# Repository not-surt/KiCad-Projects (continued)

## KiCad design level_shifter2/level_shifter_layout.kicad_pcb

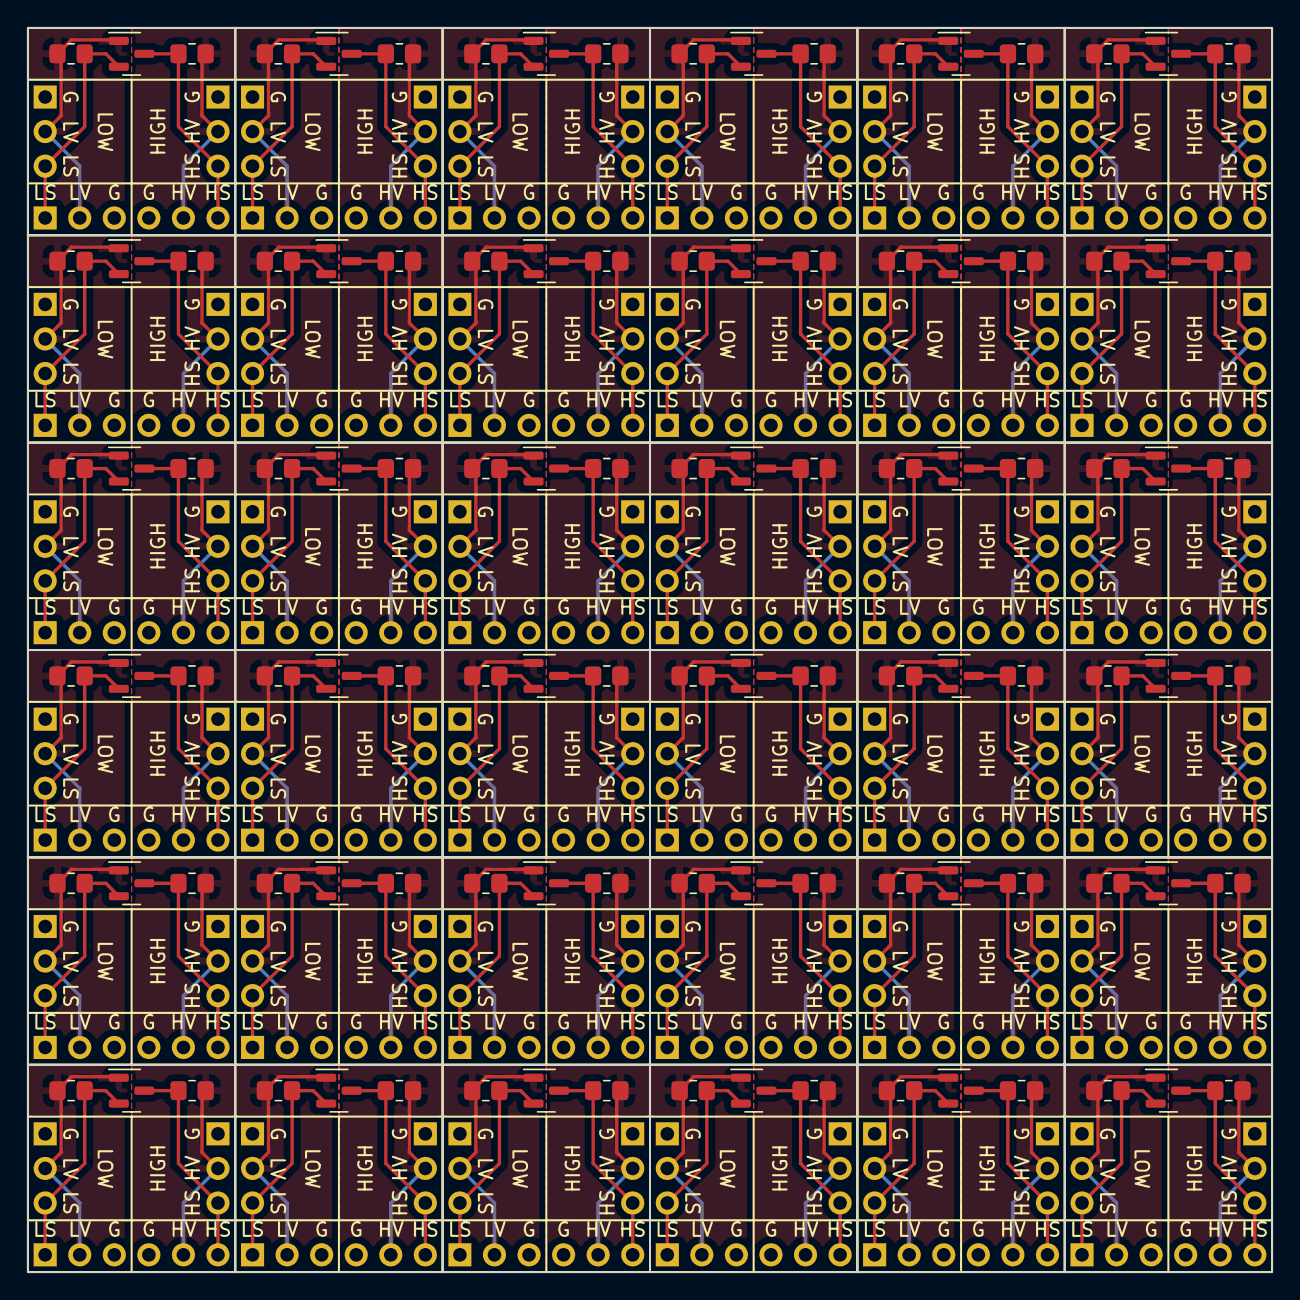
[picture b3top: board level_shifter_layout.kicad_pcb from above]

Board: 2 copper layers, 91.4 x 91.4 mm, 216 parts (0 on the bottom side), 5 nets.

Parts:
J1, J2, J3, J5, J7, J8, J10, J11, J13, J14, J16, J17, J25, J26, J28, J29, J31, J32, J34, J35, J37, J38, J40, J41, J49, J50, J52, J53, J55, J56, J58, J59, J61, J62, J64, J65, J73, J74, J76, J77, J79, J80, J82, J83, J85, J86, J88, J89, J97, J98, J100, J101, J103, J104, J106, J107, J109, J110, J112, J113, J121, J122, J124, J125, J127, J128, J130, J131, J133, J134, J136, J137: Conn_01x03; PinHeader_1x03_P2.54mm_Vertical_no_silk
J4, J6, J9, J12, J15, J18, J27, J30, J33, J36, J39, J42, J51, J54, J57, J60, J63, J66, J75, J78, J81, J84, J87, J90, J99, J102, J105, J108, J111, J114, J123, J126, J129, J132, J135, J138: Conn_01x06; PinHeader_1x06_P2.54mm_Vertical_no_silk
Q1, Q2, Q3, Q4, Q5, Q6, Q9, Q10, Q11, Q12, Q13, Q14, Q17, Q18, Q19, Q20, Q21, Q22, Q25, Q26, Q27, Q28, Q29, Q30, Q33, Q34, Q35, Q36, Q37, Q38, Q41, Q42, Q43, Q44, Q45, Q46: BSS138; SOT-23
R1, R2, R3, R4, R5, R6, R7, R8, R9, R10, R11, R12, R17, R18, R19, R20, R21, R22, R23, R24, R25, R26, R27, R28, R33, R34, R35, R36, R37, R38, R39, R40, R41, R42, R43, R44, R49, R50, R51, R52, R53, R54, R55, R56, R57, R58, R59, R60, R65, R66, R67, R68, R69, R70, R71, R72, R73, R74, R75, R76, R81, R82, R83, R84, R85, R86, R87, R88, R89, R90, R91, R92: 10K; R_0805_2012Metric_Pad1.20x1.40mm_HandSolder

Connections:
G: J1.1, J2.1, J3.1, J4.3, J4.4, J5.1, J6.3, J6.4, J7.1, J8.1, J9.3, J9.4, J10.1, J11.1, J12.3, J12.4, J13.1, J14.1, J15.3, J15.4, J16.1, J17.1, J18.3, J18.4, J25.1, J26.1, J27.3, J27.4, J28.1, J29.1, J30.3, J30.4, J31.1, J32.1, J33.3, J33.4, J34.1, J35.1, J36.3, J36.4, J37.1, J38.1, J39.3, J39.4, J40.1, J41.1, J42.3, J42.4, J49.1, J50.1, J51.3, J51.4, J52.1, J53.1, J54.3, J54.4, J55.1, J56.1, J57.3, J57.4, J58.1, J59.1, J60.3, J60.4, J61.1, J62.1, J63.3, J63.4, J64.1, J65.1, J66.3, J66.4, J73.1, J74.1, J75.3, J75.4, J76.1, J77.1, J78.3, J78.4, J79.1, J80.1, J81.3, J81.4, J82.1, J83.1, J84.3, J84.4, J85.1, J86.1, J87.3, J87.4, J88.1, J89.1, J90.3, J90.4, J97.1, J98.1, J99.3, J99.4, J100.1, J101.1, J102.3, J102.4, J103.1, J104.1, J105.3, J105.4, J106.1, J107.1, J108.3, J108.4, J109.1, J110.1, J111.3, J111.4, J112.1, J113.1, J114.3, J114.4, J121.1, J122.1, J123.3, J123.4, J124.1, J125.1, J126.3, J126.4, J127.1, J128.1, J129.3, J129.4, J130.1, J131.1, J132.3, J132.4, J133.1, J134.1, J135.3, J135.4, J136.1, J137.1, J138.3, J138.4
HS: J2.3, J4.6, J5.3, J6.6, J8.3, J9.6, J11.3, J12.6, J14.3, J15.6, J17.3, J18.6, J26.3, J27.6, J29.3, J30.6, J32.3, J33.6, J35.3, J36.6, J38.3, J39.6, J41.3, J42.6, J50.3, J51.6, J53.3, J54.6, J56.3, J57.6, J59.3, J60.6, J62.3, J63.6, J65.3, J66.6, J74.3, J75.6, J77.3, J78.6, J80.3, J81.6, J83.3, J84.6, J86.3, J87.6, J89.3, J90.6, J98.3, J99.6, J101.3, J102.6, J104.3, J105.6, J107.3, J108.6, J110.3, J111.6, J113.3, J114.6, J122.3, J123.6, J125.3, J126.6, J128.3, J129.6, J131.3, J132.6, J134.3, J135.6, J137.3, J138.6, Q1.3 (D), Q2.3 (D), Q3.3 (D), Q4.3 (D), Q5.3 (D), Q6.3 (D), Q9.3 (D), Q10.3 (D), Q11.3 (D), Q12.3 (D), Q13.3 (D), Q14.3 (D), Q17.3 (D), Q18.3 (D), Q19.3 (D), Q20.3 (D), Q21.3 (D), Q22.3 (D), Q25.3 (D), Q26.3 (D), Q27.3 (D), Q28.3 (D), Q29.3 (D), Q30.3 (D), Q33.3 (D), Q34.3 (D), Q35.3 (D), Q36.3 (D), Q37.3 (D), Q38.3 (D), Q41.3 (D), Q42.3 (D), Q43.3 (D), Q44.3 (D), Q45.3 (D), Q46.3 (D), R2.2, R4.2, R6.2, R8.2, R10.2, R12.2, R18.2, R20.2, R22.2, R24.2, R26.2, R28.2, R34.2, R36.2, R38.2, R40.2, R42.2, R44.2, R50.2, R52.2, R54.2, R56.2, R58.2, R60.2, R66.2, R68.2, R70.2, R72.2, R74.2, R76.2, R82.2, R84.2, R86.2, R88.2, R90.2, R92.2
HV: J2.2, J4.5, J5.2, J6.5, J8.2, J9.5, J11.2, J12.5, J14.2, J15.5, J17.2, J18.5, J26.2, J27.5, J29.2, J30.5, J32.2, J33.5, J35.2, J36.5, J38.2, J39.5, J41.2, J42.5, J50.2, J51.5, J53.2, J54.5, J56.2, J57.5, J59.2, J60.5, J62.2, J63.5, J65.2, J66.5, J74.2, J75.5, J77.2, J78.5, J80.2, J81.5, J83.2, J84.5, J86.2, J87.5, J89.2, J90.5, J98.2, J99.5, J101.2, J102.5, J104.2, J105.5, J107.2, J108.5, J110.2, J111.5, J113.2, J114.5, J122.2, J123.5, J125.2, J126.5, J128.2, J129.5, J131.2, J132.5, J134.2, J135.5, J137.2, J138.5, R2.1, R4.1, R6.1, R8.1, R10.1, R12.1, R18.1, R20.1, R22.1, R24.1, R26.1, R28.1, R34.1, R36.1, R38.1, R40.1, R42.1, R44.1, R50.1, R52.1, R54.1, R56.1, R58.1, R60.1, R66.1, R68.1, R70.1, R72.1, R74.1, R76.1, R82.1, R84.1, R86.1, R88.1, R90.1, R92.1
LS: J1.3, J3.3, J4.1, J6.1, J7.3, J9.1, J10.3, J12.1, J13.3, J15.1, J16.3, J18.1, J25.3, J27.1, J28.3, J30.1, J31.3, J33.1, J34.3, J36.1, J37.3, J39.1, J40.3, J42.1, J49.3, J51.1, J52.3, J54.1, J55.3, J57.1, J58.3, J60.1, J61.3, J63.1, J64.3, J66.1, J73.3, J75.1, J76.3, J78.1, J79.3, J81.1, J82.3, J84.1, J85.3, J87.1, J88.3, J90.1, J97.3, J99.1, J100.3, J102.1, J103.3, J105.1, J106.3, J108.1, J109.3, J111.1, J112.3, J114.1, J121.3, J123.1, J124.3, J126.1, J127.3, J129.1, J130.3, J132.1, J133.3, J135.1, J136.3, J138.1, Q1.2 (S), Q2.2 (S), Q3.2 (S), Q4.2 (S), Q5.2 (S), Q6.2 (S), Q9.2 (S), Q10.2 (S), Q11.2 (S), Q12.2 (S), Q13.2 (S), Q14.2 (S), Q17.2 (S), Q18.2 (S), Q19.2 (S), Q20.2 (S), Q21.2 (S), Q22.2 (S), Q25.2 (S), Q26.2 (S), Q27.2 (S), Q28.2 (S), Q29.2 (S), Q30.2 (S), Q33.2 (S), Q34.2 (S), Q35.2 (S), Q36.2 (S), Q37.2 (S), Q38.2 (S), Q41.2 (S), Q42.2 (S), Q43.2 (S), Q44.2 (S), Q45.2 (S), Q46.2 (S), R1.2, R3.2, R5.2, R7.2, R9.2, R11.2, R17.2, R19.2, R21.2, R23.2, R25.2, R27.2, R33.2, R35.2, R37.2, R39.2, R41.2, R43.2, R49.2, R51.2, R53.2, R55.2, R57.2, R59.2, R65.2, R67.2, R69.2, R71.2, R73.2, R75.2, R81.2, R83.2, R85.2, R87.2, R89.2, R91.2
LV: J1.2, J3.2, J4.2, J6.2, J7.2, J9.2, J10.2, J12.2, J13.2, J15.2, J16.2, J18.2, J25.2, J27.2, J28.2, J30.2, J31.2, J33.2, J34.2, J36.2, J37.2, J39.2, J40.2, J42.2, J49.2, J51.2, J52.2, J54.2, J55.2, J57.2, J58.2, J60.2, J61.2, J63.2, J64.2, J66.2, J73.2, J75.2, J76.2, J78.2, J79.2, J81.2, J82.2, J84.2, J85.2, J87.2, J88.2, J90.2, J97.2, J99.2, J100.2, J102.2, J103.2, J105.2, J106.2, J108.2, J109.2, J111.2, J112.2, J114.2, J121.2, J123.2, J124.2, J126.2, J127.2, J129.2, J130.2, J132.2, J133.2, J135.2, J136.2, J138.2, Q1.1 (G), Q2.1 (G), Q3.1 (G), Q4.1 (G), Q5.1 (G), Q6.1 (G), Q9.1 (G), Q10.1 (G), Q11.1 (G), Q12.1 (G), Q13.1 (G), Q14.1 (G), Q17.1 (G), Q18.1 (G), Q19.1 (G), Q20.1 (G), Q21.1 (G), Q22.1 (G), Q25.1 (G), Q26.1 (G), Q27.1 (G), Q28.1 (G), Q29.1 (G), Q30.1 (G), Q33.1 (G), Q34.1 (G), Q35.1 (G), Q36.1 (G), Q37.1 (G), Q38.1 (G), Q41.1 (G), Q42.1 (G), Q43.1 (G), Q44.1 (G), Q45.1 (G), Q46.1 (G), R1.1, R3.1, R5.1, R7.1, R9.1, R11.1, R17.1, R19.1, R21.1, R23.1, R25.1, R27.1, R33.1, R35.1, R37.1, R39.1, R41.1, R43.1, R49.1, R51.1, R53.1, R55.1, R57.1, R59.1, R65.1, R67.1, R69.1, R71.1, R73.1, R75.1, R81.1, R83.1, R85.1, R87.1, R89.1, R91.1

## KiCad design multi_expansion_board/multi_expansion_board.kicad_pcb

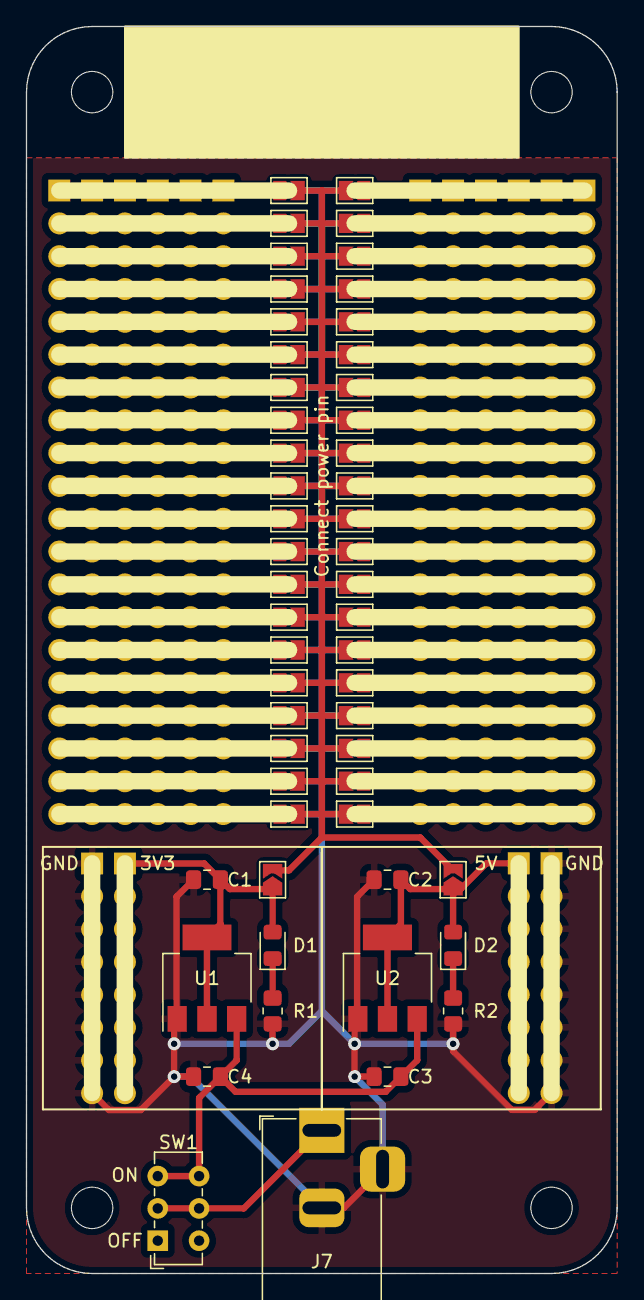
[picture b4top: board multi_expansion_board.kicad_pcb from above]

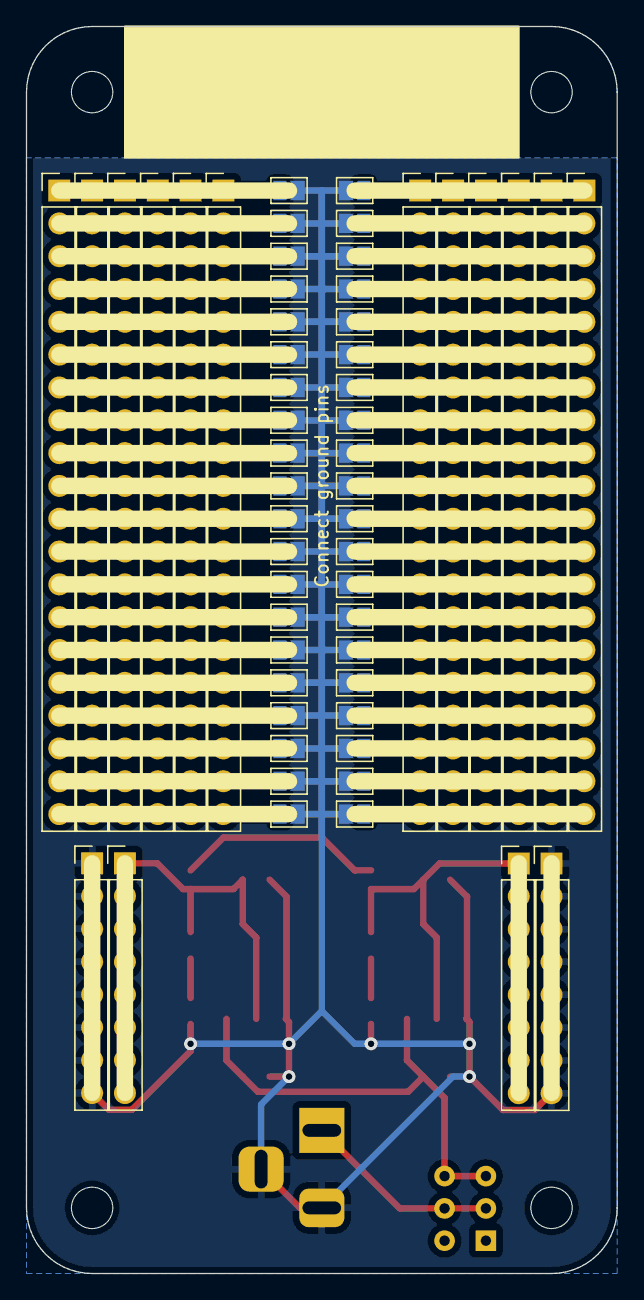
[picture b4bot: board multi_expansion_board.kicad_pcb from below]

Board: 2 copper layers, 45.7 x 96.5 mm, 110 parts (56 on the bottom side), 48 nets.

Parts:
C1, C2, C3, C4: 10uF; C_0805_2012Metric_Pad1.18x1.45mm_HandSolder
D1, D2: LED; LED_0805_2012Metric_Pad1.15x1.40mm_HandSolder
J1, J2, J3, J4, J5, J6, J8, J9, J10, J11, J12, J13: Conn_01x20; PinHeader_1x20_P2.54mm_Vertical
J7: Barrel_Jack; BarrelJack_Horizontal
J14, J15, J16, J17: Conn_01x08; PinHeader_1x08_P2.54mm_Vertical
JP1, JP2, JP3, JP4, JP5, JP6, JP7, JP8, JP9, JP10, JP11, JP12, JP13, JP14, JP15, JP16, JP17, JP18, JP19, JP20, JP21, JP22, JP23, JP24, JP25, JP26, JP27, JP28, JP29, JP30, JP31, JP32, JP33, JP34, JP35, JP36, JP37, JP38, JP39, JP40, JP41, JP42, JP43, JP44, JP45, JP46, JP47, JP48, JP49, JP50, JP51, JP52, JP53, JP54, JP55, JP56, JP57, JP58, JP59, JP60, JP61, JP62, JP63, JP64, JP65, JP66, JP67, JP68, JP69, JP70, JP71, JP72, JP73, JP74, JP75, JP76, JP77, JP78, JP79, JP80, JP81, JP82: SolderJumper_2_Open; SolderJumper-2_P1.3mm_Open_TrianglePad1.0x1.5mm
R1, R2: R; R_0805_2012Metric_Pad1.20x1.40mm_HandSolder
SW1: SW_SPST; SW_E-Switch_EG1271_DPDT
U1: AMS1117-3.3; SOT-223-3_TabPin2
U2: AMS1117-5.0; SOT-223-3_TabPin2

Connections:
+3.3V: C1.1, D1.2 (A), J15.1, J15.2, J15.3, J15.4, J15.5, J15.6, J15.7, J15.8, JP81.1 (A), U1.2 (VO)
+5V: C2.1, D2.2 (A), J16.1, J16.2, J16.3, J16.4, J16.5, J16.6, J16.7, J16.8, JP82.1 (A), U2.2 (VO)
GND: C1.2, C2.2, C3.2, C4.2, J7.2, J7.3, J14.1, J14.2, J14.3, J14.4, J14.5, J14.6, J14.7, J14.8, J17.1, J17.2, J17.3, J17.4, J17.5, J17.6, J17.7, J17.8, JP3.2 (B), JP4.2 (B), JP7.2 (B), JP8.2 (B), JP11.2 (B), JP12.2 (B), JP15.2 (B), JP16.2 (B), JP19.2 (B), JP20.2 (B), JP23.2 (B), JP24.2 (B), JP27.2 (B), JP28.2 (B), JP31.2 (B), JP32.2 (B), JP35.2 (B), JP36.2 (B), JP39.2 (B), JP40.2 (B), JP43.2 (B), JP44.2 (B), JP47.2 (B), JP48.2 (B), JP51.2 (B), JP52.2 (B), JP55.2 (B), JP56.2 (B), JP59.2 (B), JP60.2 (B), JP63.2 (B), JP64.2 (B), JP67.2 (B), JP68.2 (B), JP71.2 (B), JP72.2 (B), JP75.2 (B), JP76.2 (B), JP79.2 (B), JP80.2 (B), R1.2, R2.2, U1.1 (GND), U2.1 (GND)
unnamed: D1.1 (K), R1.1
unnamed: D2.1 (K), R2.1
unnamed: J1.1, J2.1, J3.1, J4.1, J5.1, J6.1, JP1.1 (A), JP3.1 (A)
unnamed: J1.2, J2.2, J3.2, J4.2, J5.2, J6.2, JP5.1 (A), JP7.1 (A)
unnamed: J1.3, J2.3, J3.3, J4.3, J5.3, J6.3, JP9.1 (A), JP11.1 (A)
unnamed: J1.4, J2.4, J3.4, J4.4, J5.4, J6.4, JP13.1 (A), JP15.1 (A)
unnamed: J1.5, J2.5, J3.5, J4.5, J5.5, J6.5, JP17.1 (A), JP19.1 (A)
unnamed: J1.6, J2.6, J3.6, J4.6, J5.6, J6.6, JP21.1 (A), JP23.1 (A)
unnamed: J1.7, J2.7, J3.7, J4.7, J5.7, J6.7, JP25.1 (A), JP27.1 (A)
unnamed: J1.8, J2.8, J3.8, J4.8, J5.8, J6.8, JP29.1 (A), JP31.1 (A)
unnamed: J1.9, J2.9, J3.9, J4.9, J5.9, J6.9, JP33.1 (A), JP35.1 (A)
unnamed: J1.10, J2.10, J3.10, J4.10, J5.10, J6.10, JP37.1 (A), JP39.1 (A)
unnamed: J1.11, J2.11, J3.11, J4.11, J5.11, J6.11, JP41.1 (A), JP43.1 (A)
unnamed: J1.12, J2.12, J3.12, J4.12, J5.12, J6.12, JP45.1 (A), JP47.1 (A)
unnamed: J1.13, J2.13, J3.13, J4.13, J5.13, J6.13, JP49.1 (A), JP51.1 (A)
unnamed: J1.14, J2.14, J3.14, J4.14, J5.14, J6.14, JP53.1 (A), JP55.1 (A)
unnamed: J1.15, J2.15, J3.15, J4.15, J5.15, J6.15, JP57.1 (A), JP59.1 (A)
unnamed: J1.16, J2.16, J3.16, J4.16, J5.16, J6.16, JP61.1 (A), JP63.1 (A)
unnamed: J1.17, J2.17, J3.17, J4.17, J5.17, J6.17, JP65.1 (A), JP67.1 (A)
unnamed: J1.18, J2.18, J3.18, J4.18, J5.18, J6.18, JP69.1 (A), JP71.1 (A)
unnamed: J1.19, J2.19, J3.19, J4.19, J5.19, J6.19, JP73.1 (A), JP75.1 (A)
unnamed: J1.20, J2.20, J3.20, J4.20, J5.20, J6.20, JP77.1 (A), JP79.1 (A)
unnamed: J7.1, SW1.2 (B), SW1.5
unnamed: J8.1, J9.1, J10.1, J11.1, J12.1, J13.1, JP2.1 (A), JP4.1 (A)
unnamed: J8.2, J9.2, J10.2, J11.2, J12.2, J13.2, JP6.1 (A), JP8.1 (A)
unnamed: J8.3, J9.3, J10.3, J11.3, J12.3, J13.3, JP10.1 (A), JP12.1 (A)
unnamed: J8.4, J9.4, J10.4, J11.4, J12.4, J13.4, JP14.1 (A), JP16.1 (A)
unnamed: J8.5, J9.5, J10.5, J11.5, J12.5, J13.5, JP18.1 (A), JP20.1 (A)
unnamed: J8.6, J9.6, J10.6, J11.6, J12.6, J13.6, JP22.1 (A), JP24.1 (A)
unnamed: J8.7, J9.7, J10.7, J11.7, J12.7, J13.7, JP26.1 (A), JP28.1 (A)
unnamed: J8.8, J9.8, J10.8, J11.8, J12.8, J13.8, JP30.1 (A), JP32.1 (A)
unnamed: J8.9, J9.9, J10.9, J11.9, J12.9, J13.9, JP34.1 (A), JP36.1 (A)
unnamed: J8.10, J9.10, J10.10, J11.10, J12.10, J13.10, JP38.1 (A), JP40.1 (A)
unnamed: J8.11, J9.11, J10.11, J11.11, J12.11, J13.11, JP42.1 (A), JP44.1 (A)
unnamed: J8.12, J9.12, J10.12, J11.12, J12.12, J13.12, JP46.1 (A), JP48.1 (A)
unnamed: J8.13, J9.13, J10.13, J11.13, J12.13, J13.13, JP50.1 (A), JP52.1 (A)
unnamed: J8.14, J9.14, J10.14, J11.14, J12.14, J13.14, JP54.1 (A), JP56.1 (A)
unnamed: J8.15, J9.15, J10.15, J11.15, J12.15, J13.15, JP58.1 (A), JP60.1 (A)
unnamed: J8.16, J9.16, J10.16, J11.16, J12.16, J13.16, JP62.1 (A), JP64.1 (A)
unnamed: J8.17, J9.17, J10.17, J11.17, J12.17, J13.17, JP66.1 (A), JP68.1 (A)
unnamed: J8.18, J9.18, J10.18, J11.18, J12.18, J13.18, JP70.1 (A), JP72.1 (A)
unnamed: J8.19, J9.19, J10.19, J11.19, J12.19, J13.19, JP74.1 (A), JP76.1 (A)
unnamed: J8.20, J9.20, J10.20, J11.20, J12.20, J13.20, JP78.1 (A), JP80.1 (A)
unnamed: JP1.2 (B), JP2.2 (B), JP5.2 (B), JP6.2 (B), JP9.2 (B), JP10.2 (B), JP13.2 (B), JP14.2 (B), JP17.2 (B), JP18.2 (B), JP21.2 (B), JP22.2 (B), JP25.2 (B), JP26.2 (B), JP29.2 (B), JP30.2 (B), JP33.2 (B), JP34.2 (B), JP37.2 (B), JP38.2 (B), JP41.2 (B), JP42.2 (B), JP45.2 (B), JP46.2 (B), JP49.2 (B), JP50.2 (B), JP53.2 (B), JP54.2 (B), JP57.2 (B), JP58.2 (B), JP61.2 (B), JP62.2 (B), JP65.2 (B), JP66.2 (B), JP69.2 (B), JP70.2 (B), JP73.2 (B), JP74.2 (B), JP77.2 (B), JP78.2 (B), JP81.2 (B), JP82.2 (B)
VCC: C3.1, C4.1, SW1.3, SW1.6, U1.3 (VI), U2.3 (VI)

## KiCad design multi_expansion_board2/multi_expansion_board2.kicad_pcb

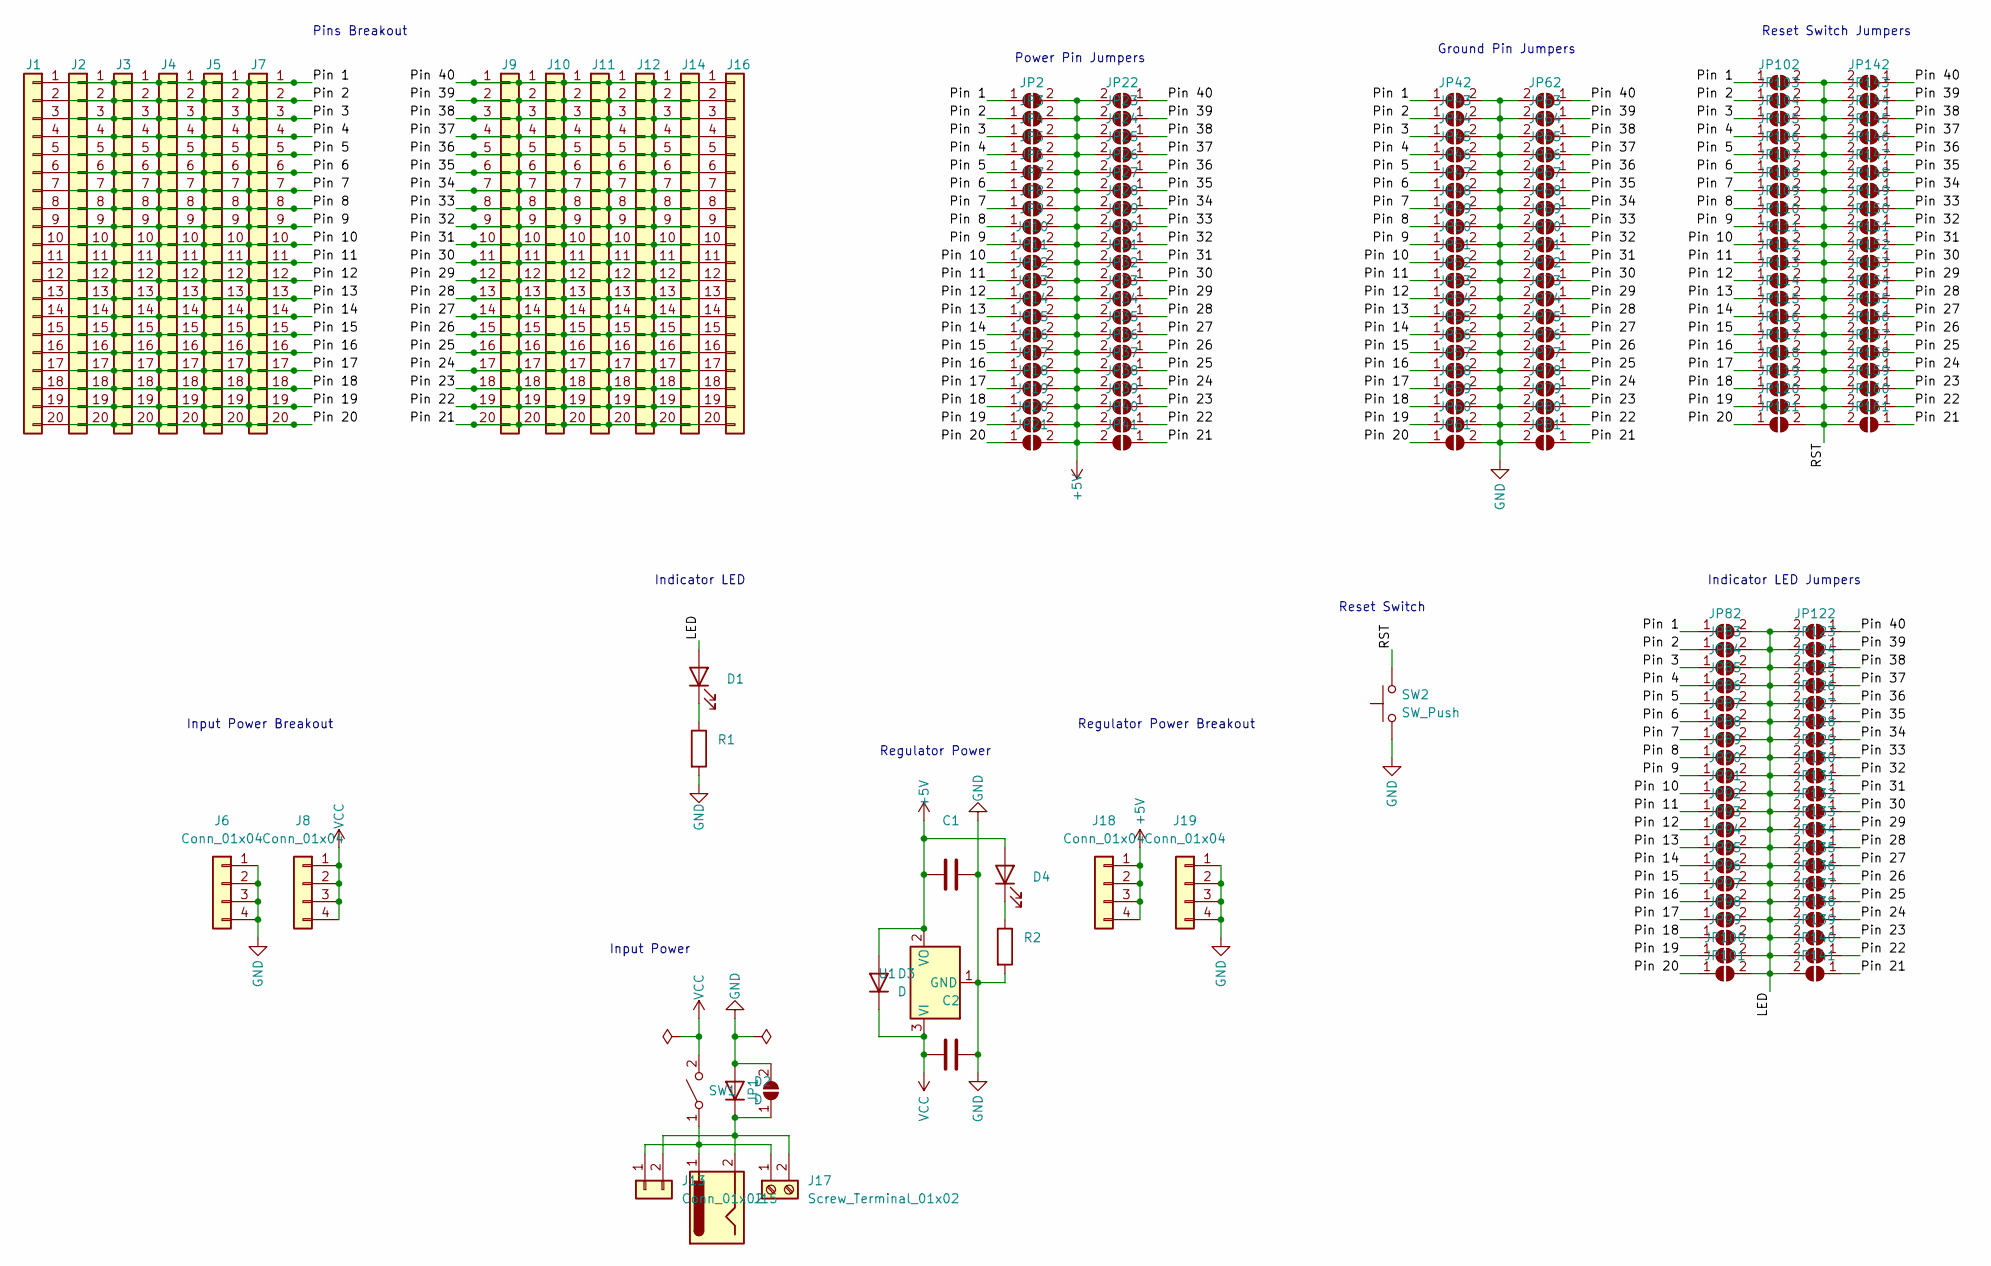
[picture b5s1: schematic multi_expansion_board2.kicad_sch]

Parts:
C1, C2: 10uF; C_0805_2012Metric_Pad1.18x1.45mm_HandSolder
D1, D4: LED; LED_0805_2012Metric_Pad1.15x1.40mm_HandSolder
D2, D3: D; D_SMA_Handsoldering
J1, J2, J3, J4, J5, J7, J9, J10, J11, J12, J14, J16: Conn_01x20; PinHeader_1x20_P2.54mm_Vertical
J6, J8, J18, J19: Conn_01x04; PinHeader_1x08_P2.54mm_Vertical
J13: Conn_01x02; PinHeader_1x02_P2.54mm_Vertical
J15: Barrel_Jack; BarrelJack_Horizontal
J17: Screw_Terminal_01x02; TerminalBlock_bornier-2_P5.08mm
JP1, JP2, JP3, JP4, JP5, JP6, JP7, JP8, JP9, JP10, JP11, JP12, JP13, JP14, JP15, JP16, JP17, JP18, JP19, JP20, JP21, JP22, JP23, JP24, JP25, JP26, JP27, JP28, JP29, JP30, JP31, JP32, JP33, JP34, JP35, JP36, JP37, JP38, JP39, JP40, JP41, JP42, JP43, JP44, JP45, JP46, JP47, JP48, JP49, JP50, JP51, JP52, JP53, JP54, JP55, JP56, JP57, JP58, JP59, JP60, JP61, JP62, JP63, JP64, JP65, JP66, JP67, JP68, JP69, JP70, JP71, JP72, JP73, JP74, JP75, JP76, JP77, JP78, JP79, JP80, JP81, JP82, JP83, JP84, JP85, JP86, JP87, JP88, JP89, JP90, JP91, JP92, JP93, JP94, JP95, JP96, JP97, JP98, JP99, JP100, JP101, JP102, JP103, JP104, JP105, JP106, JP107, JP108, JP109, JP110, JP111, JP112, JP113, JP114, JP115, JP116, JP117, JP118, JP119, JP120, JP121, JP122, JP123, JP124, JP125, JP126, JP127, JP128, JP129, JP130, JP131, JP132, JP133, JP134, JP135, JP136, JP137, JP138, JP139, JP140, JP141, JP142, JP143, JP144, JP145, JP146, JP147, JP148, JP149, JP150, JP151, JP152, JP153, JP154, JP155, JP156, JP157, JP158, JP159, JP160, JP161: SolderJumper_2_Open; SolderJumper-2_P1.3mm_Open_RoundedPad1.0x1.5mm
R1, R2: R; R_0805_2012Metric_Pad1.20x1.40mm_HandSolder
SW1: SW_SPST; SW_E-Switch_EG1271_DPDT
SW2: SW_Push; SW_PUSH_6mm
U1: AMS1117-5.0; SOT-223-3_TabPin2

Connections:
+5V: C1.1, D3.2 (A), D4.2 (A), J18.1, J18.2, J18.3, J18.4, JP2.2 (B), JP3.2 (B), JP4.2 (B), JP5.2 (B), JP6.2 (B), JP7.2 (B), JP8.2 (B), JP9.2 (B), JP10.2 (B), JP11.2 (B), JP12.2 (B), JP13.2 (B), JP14.2 (B), JP15.2 (B), JP16.2 (B), JP17.2 (B), JP18.2 (B), JP19.2 (B), JP20.2 (B), JP21.2 (B), JP22.2 (B), JP23.2 (B), JP24.2 (B), JP25.2 (B), JP26.2 (B), JP27.2 (B), JP28.2 (B), JP29.2 (B), JP30.2 (B), JP31.2 (B), JP32.2 (B), JP33.2 (B), JP34.2 (B), JP35.2 (B), JP36.2 (B), JP37.2 (B), JP38.2 (B), JP39.2 (B), JP40.2 (B), JP41.2 (B), U1.2 (VO)
/LED: D1.2 (A), JP82.2 (B), JP83.2 (B), JP84.2 (B), JP85.2 (B), JP86.2 (B), JP87.2 (B), JP88.2 (B), JP89.2 (B), JP90.2 (B), JP91.2 (B), JP92.2 (B), JP93.2 (B), JP94.2 (B), JP95.2 (B), JP96.2 (B), JP97.2 (B), JP98.2 (B), JP99.2 (B), JP100.2 (B), JP101.2 (B), JP122.2 (B), JP123.2 (B), JP124.2 (B), JP125.2 (B), JP126.2 (B), JP127.2 (B), JP128.2 (B), JP129.2 (B), JP130.2 (B), JP131.2 (B), JP132.2 (B), JP133.2 (B), JP134.2 (B), JP135.2 (B), JP136.2 (B), JP137.2 (B), JP138.2 (B), JP139.2 (B), JP140.2 (B), JP141.2 (B)
/Pin 1: J1.1, J2.1, J3.1, J4.1, J5.1, J7.1, JP2.1 (A), JP42.1 (A), JP82.1 (A), JP102.1 (A)
/Pin 2: J1.2, J2.2, J3.2, J4.2, J5.2, J7.2, JP3.1 (A), JP43.1 (A), JP83.1 (A), JP103.1 (A)
/Pin 3: J1.3, J2.3, J3.3, J4.3, J5.3, J7.3, JP4.1 (A), JP44.1 (A), JP84.1 (A), JP104.1 (A)
/Pin 4: J1.4, J2.4, J3.4, J4.4, J5.4, J7.4, JP5.1 (A), JP45.1 (A), JP85.1 (A), JP105.1 (A)
/Pin 5: J1.5, J2.5, J3.5, J4.5, J5.5, J7.5, JP6.1 (A), JP46.1 (A), JP86.1 (A), JP106.1 (A)
/Pin 6: J1.6, J2.6, J3.6, J4.6, J5.6, J7.6, JP7.1 (A), JP47.1 (A), JP87.1 (A), JP107.1 (A)
/Pin 7: J1.7, J2.7, J3.7, J4.7, J5.7, J7.7, JP8.1 (A), JP48.1 (A), JP88.1 (A), JP108.1 (A)
/Pin 8: J1.8, J2.8, J3.8, J4.8, J5.8, J7.8, JP9.1 (A), JP49.1 (A), JP89.1 (A), JP109.1 (A)
/Pin 9: J1.9, J2.9, J3.9, J4.9, J5.9, J7.9, JP10.1 (A), JP50.1 (A), JP90.1 (A), JP110.1 (A)
/Pin 10: J1.10, J2.10, J3.10, J4.10, J5.10, J7.10, JP11.1 (A), JP51.1 (A), JP91.1 (A), JP111.1 (A)
/Pin 11: J1.11, J2.11, J3.11, J4.11, J5.11, J7.11, JP12.1 (A), JP52.1 (A), JP92.1 (A), JP112.1 (A)
/Pin 12: J1.12, J2.12, J3.12, J4.12, J5.12, J7.12, JP13.1 (A), JP53.1 (A), JP93.1 (A), JP113.1 (A)
/Pin 13: J1.13, J2.13, J3.13, J4.13, J5.13, J7.13, JP14.1 (A), JP54.1 (A), JP94.1 (A), JP114.1 (A)
/Pin 14: J1.14, J2.14, J3.14, J4.14, J5.14, J7.14, JP15.1 (A), JP55.1 (A), JP95.1 (A), JP115.1 (A)
/Pin 15: J1.15, J2.15, J3.15, J4.15, J5.15, J7.15, JP16.1 (A), JP56.1 (A), JP96.1 (A), JP116.1 (A)
/Pin 16: J1.16, J2.16, J3.16, J4.16, J5.16, J7.16, JP17.1 (A), JP57.1 (A), JP97.1 (A), JP117.1 (A)
/Pin 17: J1.17, J2.17, J3.17, J4.17, J5.17, J7.17, JP18.1 (A), JP58.1 (A), JP98.1 (A), JP118.1 (A)
/Pin 18: J1.18, J2.18, J3.18, J4.18, J5.18, J7.18, JP19.1 (A), JP59.1 (A), JP99.1 (A), JP119.1 (A)
/Pin 19: J1.19, J2.19, J3.19, J4.19, J5.19, J7.19, JP20.1 (A), JP60.1 (A), JP100.1 (A), JP120.1 (A)
/Pin 20: J1.20, J2.20, J3.20, J4.20, J5.20, J7.20, JP21.1 (A), JP61.1 (A), JP101.1 (A), JP121.1 (A)
/Pin 21: J9.20, J10.20, J11.20, J12.20, J14.20, J16.20, JP41.1 (A), JP81.1 (A), JP141.1 (A), JP161.1 (A)
/Pin 22: J9.19, J10.19, J11.19, J12.19, J14.19, J16.19, JP40.1 (A), JP80.1 (A), JP140.1 (A), JP160.1 (A)
/Pin 23: J9.18, J10.18, J11.18, J12.18, J14.18, J16.18, JP39.1 (A), JP79.1 (A), JP139.1 (A), JP159.1 (A)
/Pin 24: J9.17, J10.17, J11.17, J12.17, J14.17, J16.17, JP38.1 (A), JP78.1 (A), JP138.1 (A), JP158.1 (A)
/Pin 25: J9.16, J10.16, J11.16, J12.16, J14.16, J16.16, JP37.1 (A), JP77.1 (A), JP137.1 (A), JP157.1 (A)
/Pin 26: J9.15, J10.15, J11.15, J12.15, J14.15, J16.15, JP36.1 (A), JP76.1 (A), JP136.1 (A), JP156.1 (A)
/Pin 27: J9.14, J10.14, J11.14, J12.14, J14.14, J16.14, JP35.1 (A), JP75.1 (A), JP135.1 (A), JP155.1 (A)
/Pin 28: J9.13, J10.13, J11.13, J12.13, J14.13, J16.13, JP34.1 (A), JP74.1 (A), JP134.1 (A), JP154.1 (A)
/Pin 29: J9.12, J10.12, J11.12, J12.12, J14.12, J16.12, JP33.1 (A), JP73.1 (A), JP133.1 (A), JP153.1 (A)
/Pin 30: J9.11, J10.11, J11.11, J12.11, J14.11, J16.11, JP32.1 (A), JP72.1 (A), JP132.1 (A), JP152.1 (A)
/Pin 31: J9.10, J10.10, J11.10, J12.10, J14.10, J16.10, JP31.1 (A), JP71.1 (A), JP131.1 (A), JP151.1 (A)
/Pin 32: J9.9, J10.9, J11.9, J12.9, J14.9, J16.9, JP30.1 (A), JP70.1 (A), JP130.1 (A), JP150.1 (A)
/Pin 33: J9.8, J10.8, J11.8, J12.8, J14.8, J16.8, JP29.1 (A), JP69.1 (A), JP129.1 (A), JP149.1 (A)
/Pin 34: J9.7, J10.7, J11.7, J12.7, J14.7, J16.7, JP28.1 (A), JP68.1 (A), JP128.1 (A), JP148.1 (A)
/Pin 35: J9.6, J10.6, J11.6, J12.6, J14.6, J16.6, JP27.1 (A), JP67.1 (A), JP127.1 (A), JP147.1 (A)
/Pin 36: J9.5, J10.5, J11.5, J12.5, J14.5, J16.5, JP26.1 (A), JP66.1 (A), JP126.1 (A), JP146.1 (A)
/Pin 37: J9.4, J10.4, J11.4, J12.4, J14.4, J16.4, JP25.1 (A), JP65.1 (A), JP125.1 (A), JP145.1 (A)
/Pin 38: J9.3, J10.3, J11.3, J12.3, J14.3, J16.3, JP24.1 (A), JP64.1 (A), JP124.1 (A), JP144.1 (A)
/Pin 39: J9.2, J10.2, J11.2, J12.2, J14.2, J16.2, JP23.1 (A), JP63.1 (A), JP123.1 (A), JP143.1 (A)
/Pin 40: J9.1, J10.1, J11.1, J12.1, J14.1, J16.1, JP22.1 (A), JP62.1 (A), JP122.1 (A), JP142.1 (A)
/RST: JP102.2 (B), JP103.2 (B), JP104.2 (B), JP105.2 (B), JP106.2 (B), JP107.2 (B), JP108.2 (B), JP109.2 (B), JP110.2 (B), JP111.2 (B), JP112.2 (B), JP113.2 (B), JP114.2 (B), JP115.2 (B), JP116.2 (B), JP117.2 (B), JP118.2 (B), JP119.2 (B), JP120.2 (B), JP121.2 (B), JP142.2 (B), JP143.2 (B), JP144.2 (B), JP145.2 (B), JP146.2 (B), JP147.2 (B), JP148.2 (B), JP149.2 (B), JP150.2 (B), JP151.2 (B), JP152.2 (B), JP153.2 (B), JP154.2 (B), JP155.2 (B), JP156.2 (B), JP157.2 (B), JP158.2 (B), JP159.2 (B), JP160.2 (B), JP161.2 (B), SW2.2
GND: C1.2, C2.2, D2.2 (A), J6.1, J6.2, J6.3, J6.4, J19.1, J19.2, J19.3, J19.4, JP1.2 (B), JP42.2 (B), JP43.2 (B), JP44.2 (B), JP45.2 (B), JP46.2 (B), JP47.2 (B), JP48.2 (B), JP49.2 (B), JP50.2 (B), JP51.2 (B), JP52.2 (B), JP53.2 (B), JP54.2 (B), JP55.2 (B), JP56.2 (B), JP57.2 (B), JP58.2 (B), JP59.2 (B), JP60.2 (B), JP61.2 (B), JP62.2 (B), JP63.2 (B), JP64.2 (B), JP65.2 (B), JP66.2 (B), JP67.2 (B), JP68.2 (B), JP69.2 (B), JP70.2 (B), JP71.2 (B), JP72.2 (B), JP73.2 (B), JP74.2 (B), JP75.2 (B), JP76.2 (B), JP77.2 (B), JP78.2 (B), JP79.2 (B), JP80.2 (B), JP81.2 (B), R1.2, R2.2, SW2.1, U1.1 (GND)
unnamed: D1.1 (K), R1.1
unnamed: D2.1 (K), J13.2, J15.2, J15.3, J17.2, JP1.1 (A)
unnamed: D4.1 (K), R2.1
unnamed: J13.1, J15.1, J17.1, SW1.1 (A), SW1.4
VCC: C2.1, D3.1 (K), J8.1, J8.2, J8.3, J8.4, SW1.2 (B), SW1.5, U1.3 (VI)

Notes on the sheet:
Reset Switch
Pins Breakout
Regulator Power
Power Pin Jumpers
Input Power
Reset Switch Jumpers
Input Power Breakout
Regulator Power Breakout
Ground Pin Jumpers
Indicator LED Jumpers
Indicator LED

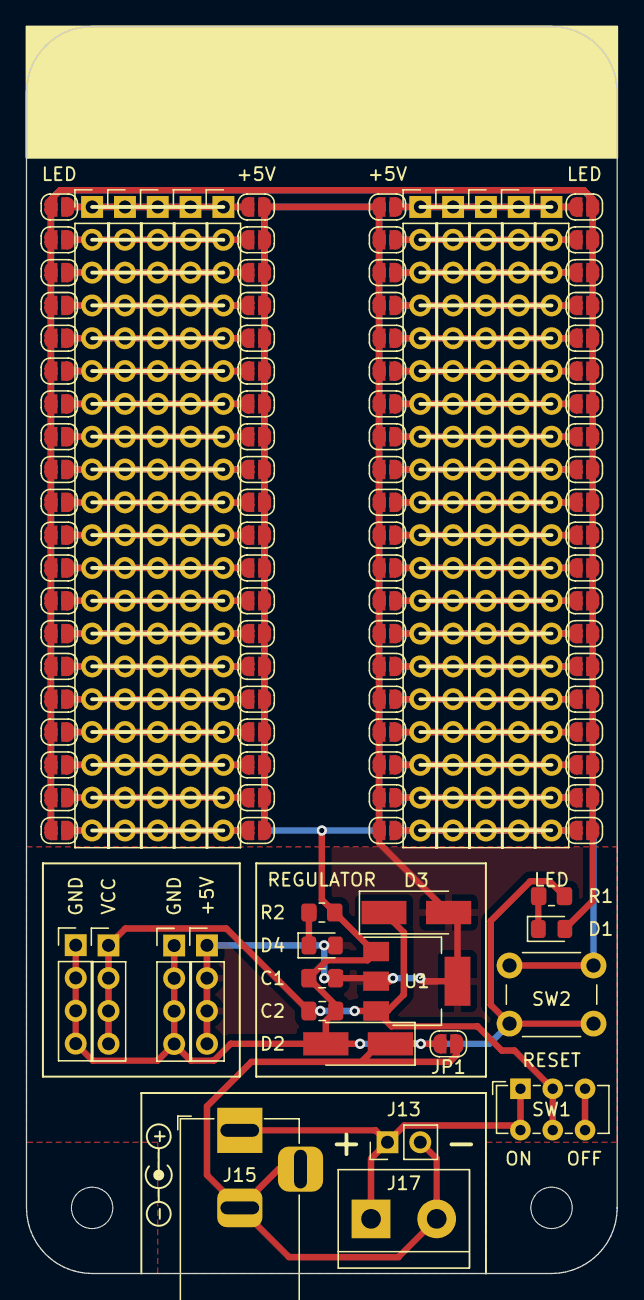
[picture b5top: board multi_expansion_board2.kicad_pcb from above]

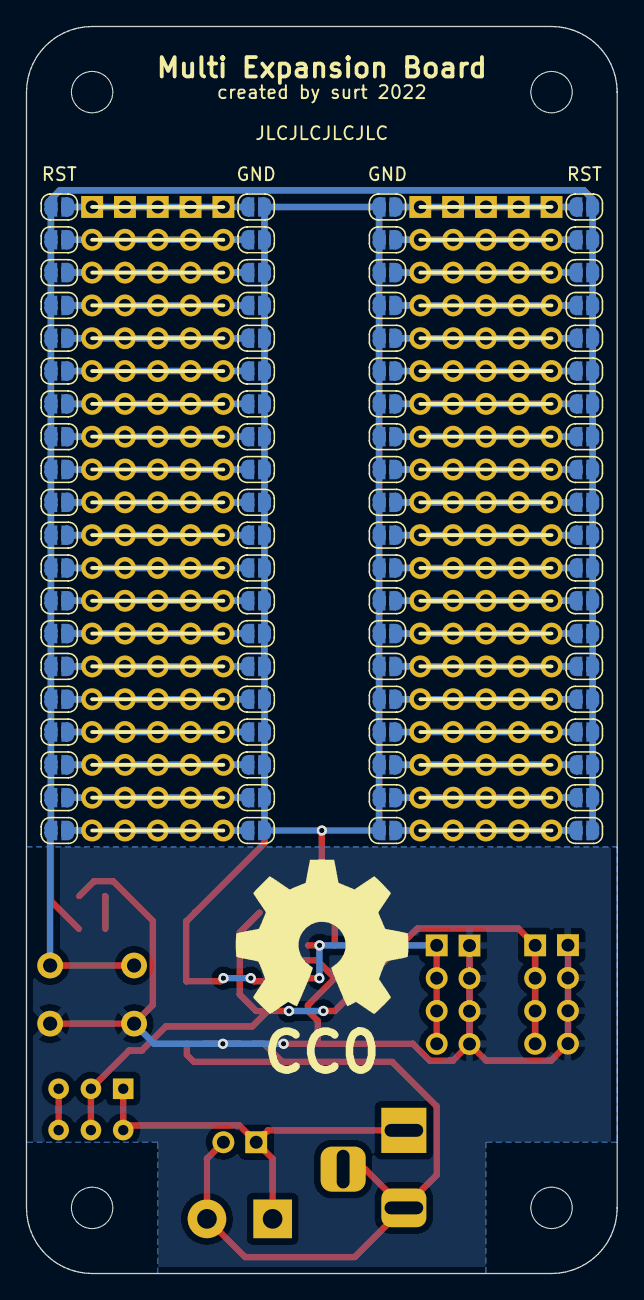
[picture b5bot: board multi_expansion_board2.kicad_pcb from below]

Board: 2 copper layers, 45.7 x 96.5 mm, 189 parts (80 on the bottom side), 49 nets.
